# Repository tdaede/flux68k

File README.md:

flux68k
=======

The flux68k is an adapter board that allows usage of Gotek floppy drive emulators running [FlashFloppy](https://github.com/keirf/flashfloppy) firmware with the Sharp X68000 line of computers.

Requirements
------------

1. Two Gotek floppy emulators based on the AT32F435 with SFRKC30.AT4.35 PCB revision (sold as FlashFloppy+ compatible).

2. Two USB flash drives.

3. flux68k PCB.

4. DC +5V power supply with a 6x2.1mm center positive barrel jack (unless using auto switch board)

5. Male to male DB37 cable.

Installation
------------

1. Set the jumpers on each of the Gotek emulators to S0 and MOR.

2. Install the emulators into the flux68k PCB, being careful to line up the power connectors.

3. Plug in the +5V power supply and ensure that both emulators power on.

4. Build the following branch of FlashFloppy, and flash it to to the Gotek. https://github.com/keirf/flashfloppy/pull/781

5. Copy the [example FF.CFG](https://github.com/keirf/flashfloppy/blob/a0a06fc15bd6ab05d6b62a67390bd5e57fd1853e/examples/FF.CFG) to each of the USB sticks and change the pin02 line to:
``` ini
pin02 = in
```

6. Set the switch on the back of the flux68k to drives 2-3.

7. Plug in the DB37 cable between the X68000 and the flux68k.

Usage
-----

Copy floppy images to the USB flash drives and access or boot from them from the X68000. More detailed information on using FlashFloppy can be found at (FlashFloppy's documentation)[https://github.com/keirf/flashfloppy/wiki].

Notes
-----

* XDF images must be renamed to have the .img extension.

* Many applications do not boot correctly from drives 2-3. For these, the rear switch must be set to drives 0-1, and the X68000's internal drives disconnected (unless the auto switch board is used, see below). On compact models, there is a switch on the back of the X68000 to switch the internal drive assigments to 2-3.

* The flux68k must be powered when attached to the X68000 or floppies may not read correctly.

* FlashFloppy currently ignores the motorized eject signal, so the floppy must be manually ejected (by pushing the rotary knob) if an application tries to automatically eject a floppy.

Auto switch board
=================

Optionally, a mod can be installed on non-compact models to automatically switch the internal floppy drive assignments. In addition, this board will also supply power to the external floppy emulators, so that an external power supply is not needed.

Requirements
------------

1. Auto switcher board

2. 34 pin IDC cable, at least 20cm Long

3. +5V internal power cable, either a [Molex to berg connector cable](https://www.crystalfontz.com/product/wrpwry12-four-pin-power-splitter-cable) or a custom made cable that attaches to one of the 3 pin berg connections for the floppy drives or HDD.

Installation
------------

1. Remove the left panel of the X68000.

2. Disconnect the SCSI cable from the external SCSI connector PCB, if present.

3. Disconnect the floppy cable from the external floppy connector PCB.

4. Unscrew and remove the SCSI/floppy connector module via the two plastic tapping screws holding it in place.

5. Remove the SCSI connector PCB from the module by removing the two machine screws holding it in place.

6. Remove the floppy connector PCB from the mdoule by removing the two machine screws holding it in place. Note the relative positions of the bracket and EMI shielding.

7. Attach the new 34 pin IDC cable to the "MB" connector on the auto switcher PCB.

8. Attach the +5V power cable to the swapper PCB.

9. Install the auto switcher PCB on the original metal bracket / EMI shield using the two machine screws.

10. Install the SCSI connector board (if present) on top of the swapper PCB with two machine screws.

11. Install the external connector module back into the X68000 using the two plastic tapping screws.

12. Attach the +5V cable to the appropriate location (the molex connector if using a molex to berg cable).

13. Connect the existing 34 pin floppy IDC cable coming off of the floppy drives to the "FD" connector on the swapper PCB.

14. Disconnect the other end of the existing 34 pin floppy IDC cable from the motherboard connector at the base of the X68000. Leave this disconnected inside the machine.

15. Connect the other end of the new 34 pin IDC cable (connected to the "MB" connector on the switcher PCB) to the motherboard connector at the base of the X68000.

16. Reinstall the left panel of the X68000.

Notes
-----

* The auto switcher PCB uses the previously unused pin 3 of the 37-pin connector as the switch signal. When left floating or high, it switches the internal drives to 0-1. When pulled low, it switches the internal drives to 2-3.

* The auto swticher PCB uses unused pins 18 and 19 of the 37-pin connector to send +5V power to the external floppy emulator. Each pin is protected by a 250mA PTC fuse.

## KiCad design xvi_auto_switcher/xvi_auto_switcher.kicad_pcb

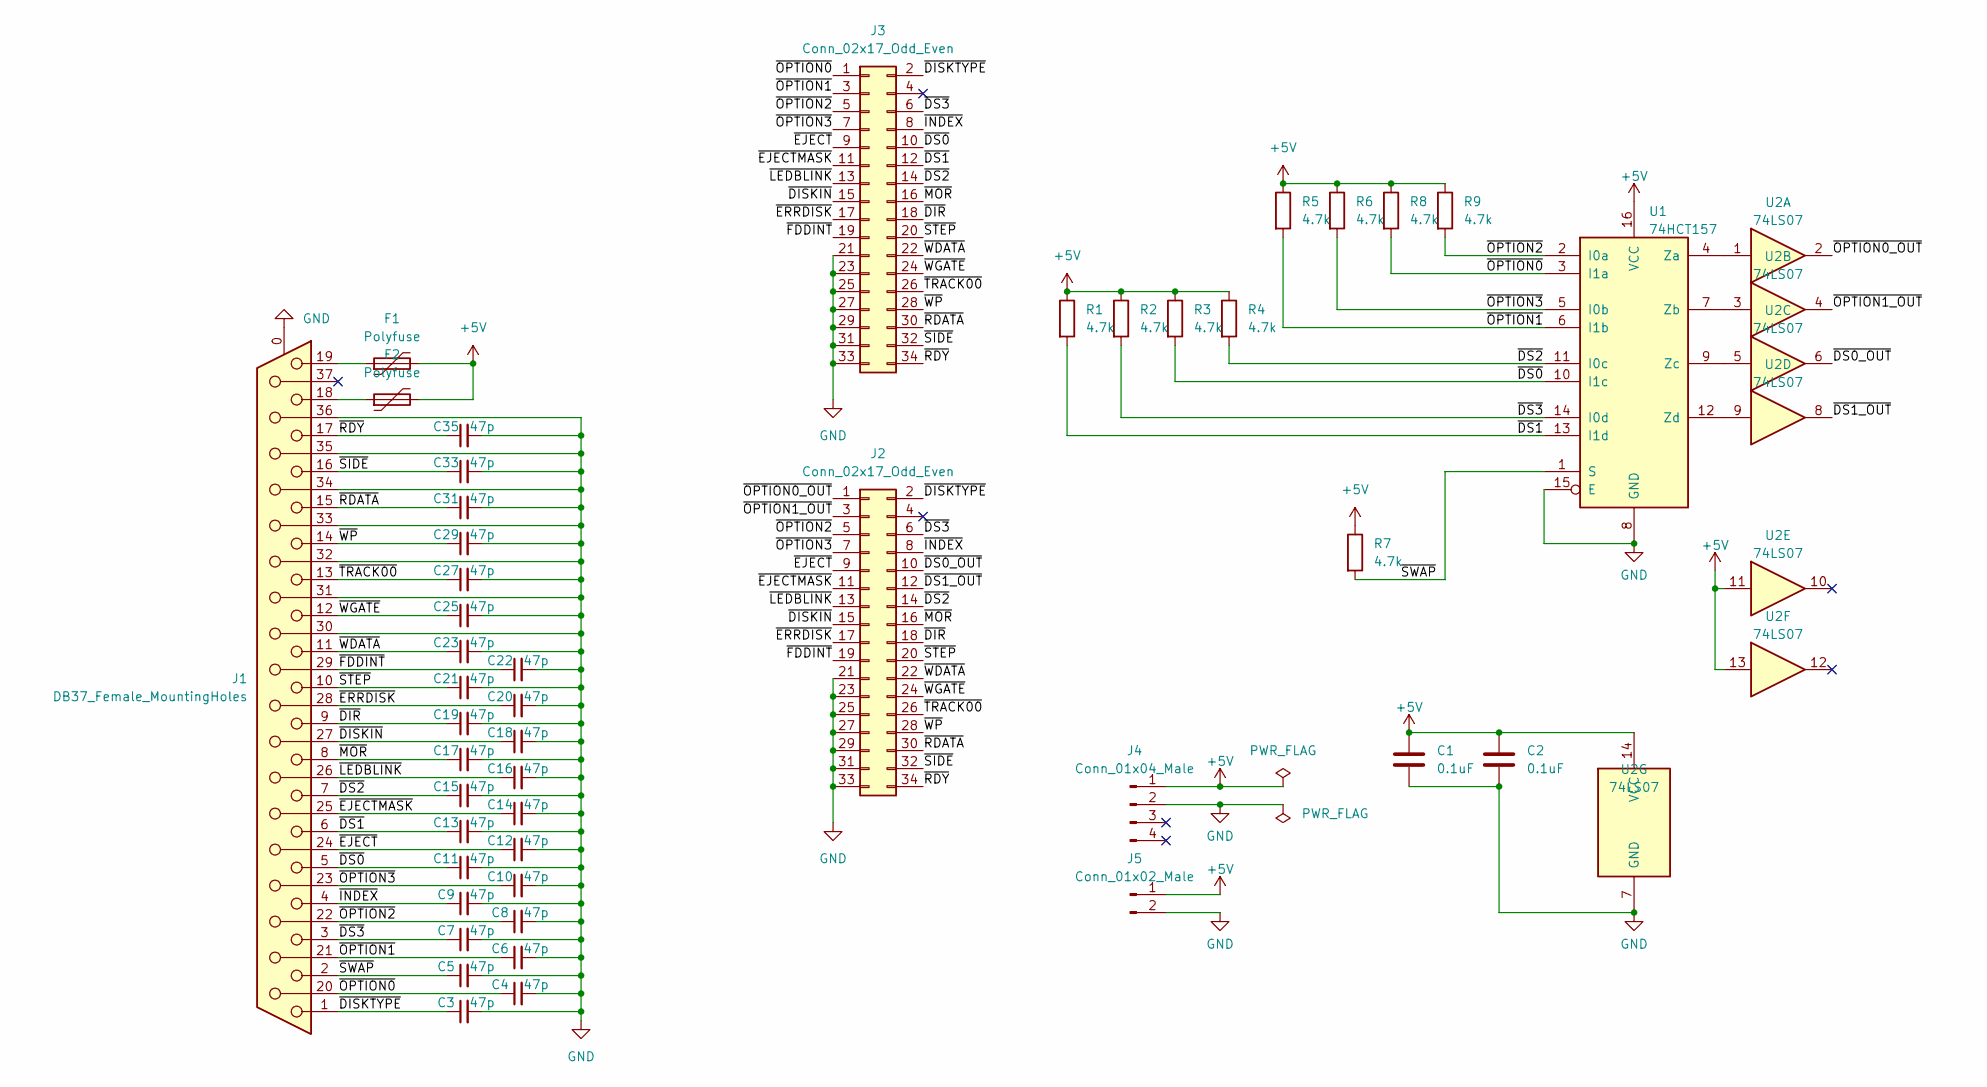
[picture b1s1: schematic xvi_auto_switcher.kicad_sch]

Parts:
C1, C2: 0.1uF; C_0603_1608Metric; Digikey 311-1088-1-ND
C3, C4, C5, C6, C7, C8, C9, C10, C11, C12, C13, C14, C15, C16, C17, C18, C19, C20, C21, C22, C23, C25, C27, C29, C31, C33, C35: 47p; C_0603_1608Metric; Digikey 311-1065-1-ND
F1, F2: Polyfuse; R_1206_3216Metric; Digikey 507-1799-1-ND
J1: DB37_Female_MountingHoles; DSUB-37_Female_Horizontal_P2.77x2.84mm_EdgePinOffset7.70mm_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; Digikey A32114-ND
J2, J3: Conn_02x17_Odd_Even; IDC-Header_2x17_P2.54mm_Vertical; Digikey ED10528-ND
J4: Conn_01x04_Male; PinHeader_1x04_P2.54mm_Horizontal; Digikey A112643-ND
J5: Conn_01x02_Male; PinHeader_1x02_P2.54mm_Vertical; Digikey DNP
R1, R2, R3, R4, R5, R6, R7, R8, R9: 4.7k; R_0603_1608Metric; Digikey 311-4.70KHRCT-ND
U1: 74HCT157; SOIC-16_3.9x9.9mm_P1.27mm; Digikey 296-31835-1-ND
U2: 74LS07; SOIC-14_3.9x8.7mm_P1.27mm; Digikey 296-14877-1-ND

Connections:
+5V: C1.1, C2.1, F1.2, F2.2, J4.1, J5.1, R1.1, R2.1, R3.1, R4.1, R5.1, R6.1, R7.1, R8.1, R9.1, U1.16 (VCC), U2.11, U2.13, U2.14 (VCC)
/~DIR: C19.1, J1.9, J2.18, J3.18
/~DISKIN: C18.1, J1.27, J2.15, J3.15
/~DISKTYPE: C3.1, J1.1, J2.2, J3.2
/~DS0_OUT: J2.10, U2.6
/~DS0: C11.1, J1.5, J3.10, R3.2, U1.10 (I1c)
/~DS1_OUT: J2.12, U2.8
/~DS1: C13.1, J1.6, J3.12, R1.2, U1.13 (I1d)
/~DS2: C15.1, J1.7, J2.14, J3.14, R4.2, U1.11 (I0c)
/~DS3: C7.1, J1.3, J2.6, J3.6, R2.2, U1.14 (I0d)
/~EJECTMASK: C14.1, J1.25, J2.11, J3.11
/~EJECT: C12.1, J1.24, J2.9, J3.9
/~ERRDISK: C20.1, J1.28, J2.17, J3.17
/~FDDINT: C22.1, J1.29, J2.19, J3.19
/~INDEX: C9.1, J1.4, J2.8, J3.8
/~LEDBLINK: C16.1, J1.26, J2.13, J3.13
/~MOR: C17.1, J1.8, J2.16, J3.16
/~OPTION0_OUT: J2.1, U2.2
/~OPTION0: C4.1, J1.20, J3.1, R8.2, U1.3 (I1a)
/~OPTION1_OUT: J2.3, U2.4
/~OPTION1: C6.1, J1.21, J3.3, R5.2, U1.6 (I1b)
/~OPTION2: C8.1, J1.22, J2.5, J3.5, R9.2, U1.2 (I0a)
/~OPTION3: C10.1, J1.23, J2.7, J3.7, R6.2, U1.5 (I0b)
/~RDATA: C31.1, J1.15, J2.30, J3.30
/~RDY: C35.1, J1.17, J2.34, J3.34
/~SIDE: C33.1, J1.16, J2.32, J3.32
/~STEP: C21.1, J1.10, J2.20, J3.20
/~SWAP: C5.1, J1.2, R7.2, U1.1 (S)
/~TRACK00: C27.1, J1.13, J2.26, J3.26
/~WDATA: C23.1, J1.11, J2.22, J3.22
/~WGATE: C25.1, J1.12, J2.24, J3.24
/~WP: C29.1, J1.14, J2.28, J3.28
GND: C1.2, C2.2, C3.2, C4.2, C5.2, C6.2, C7.2, C8.2, C9.2, C10.2, C11.2, C12.2, C13.2, C14.2, C15.2, C16.2, C17.2, C18.2, C19.2, C20.2, C21.2, C22.2, C23.2, C25.2, C27.2, C29.2, C31.2, C33.2, C35.2, J1.0 (PAD), J1.30, J1.31, J1.32, J1.33, J1.34, J1.35, J1.36, J2.21, J2.23, J2.25, J2.27, J2.29, J2.31, J2.33, J3.21, J3.23, J3.25, J3.27, J3.29, J3.31, J3.33, J4.2, J5.2, U1.8 (GND), U1.15 (E), U2.7 (GND)
unnamed: F1.1, J1.19
unnamed: F2.1, J1.18
unnamed: U1.4 (Za), U2.1
unnamed: U1.7 (Zb), U2.3
unnamed: U1.9 (Zc), U2.5
unnamed: U1.12 (Zd), U2.9

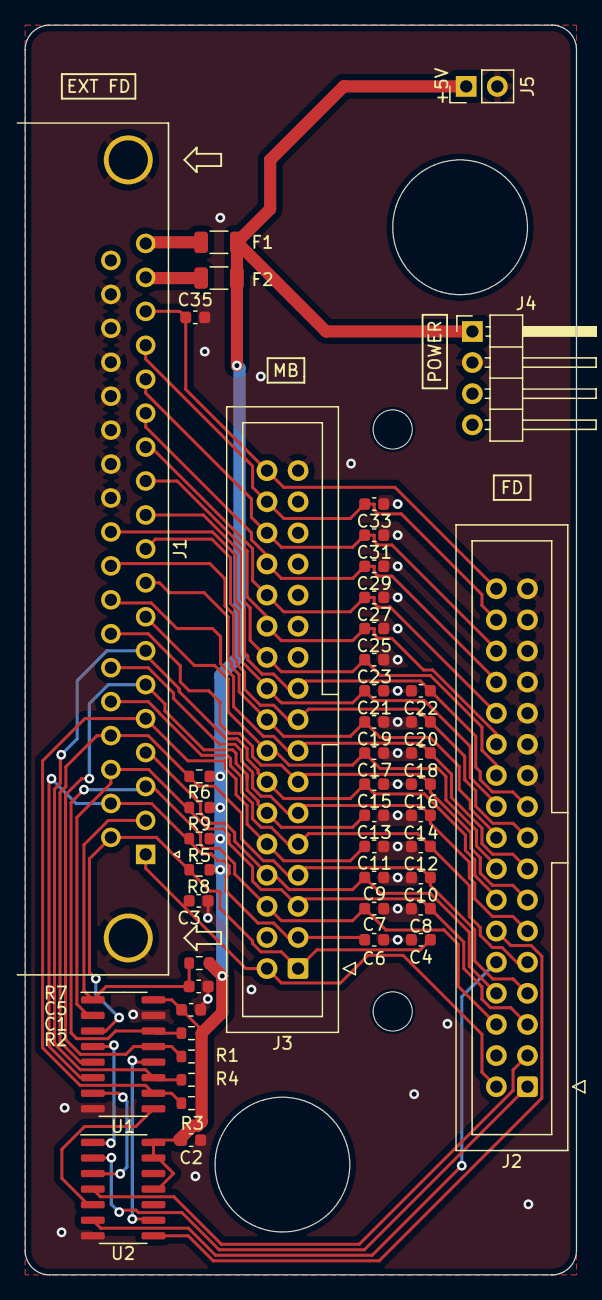
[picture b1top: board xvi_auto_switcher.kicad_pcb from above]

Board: 2 copper layers, 45.0 x 102.0 mm, 47 parts (0 on the bottom side), 39 nets.

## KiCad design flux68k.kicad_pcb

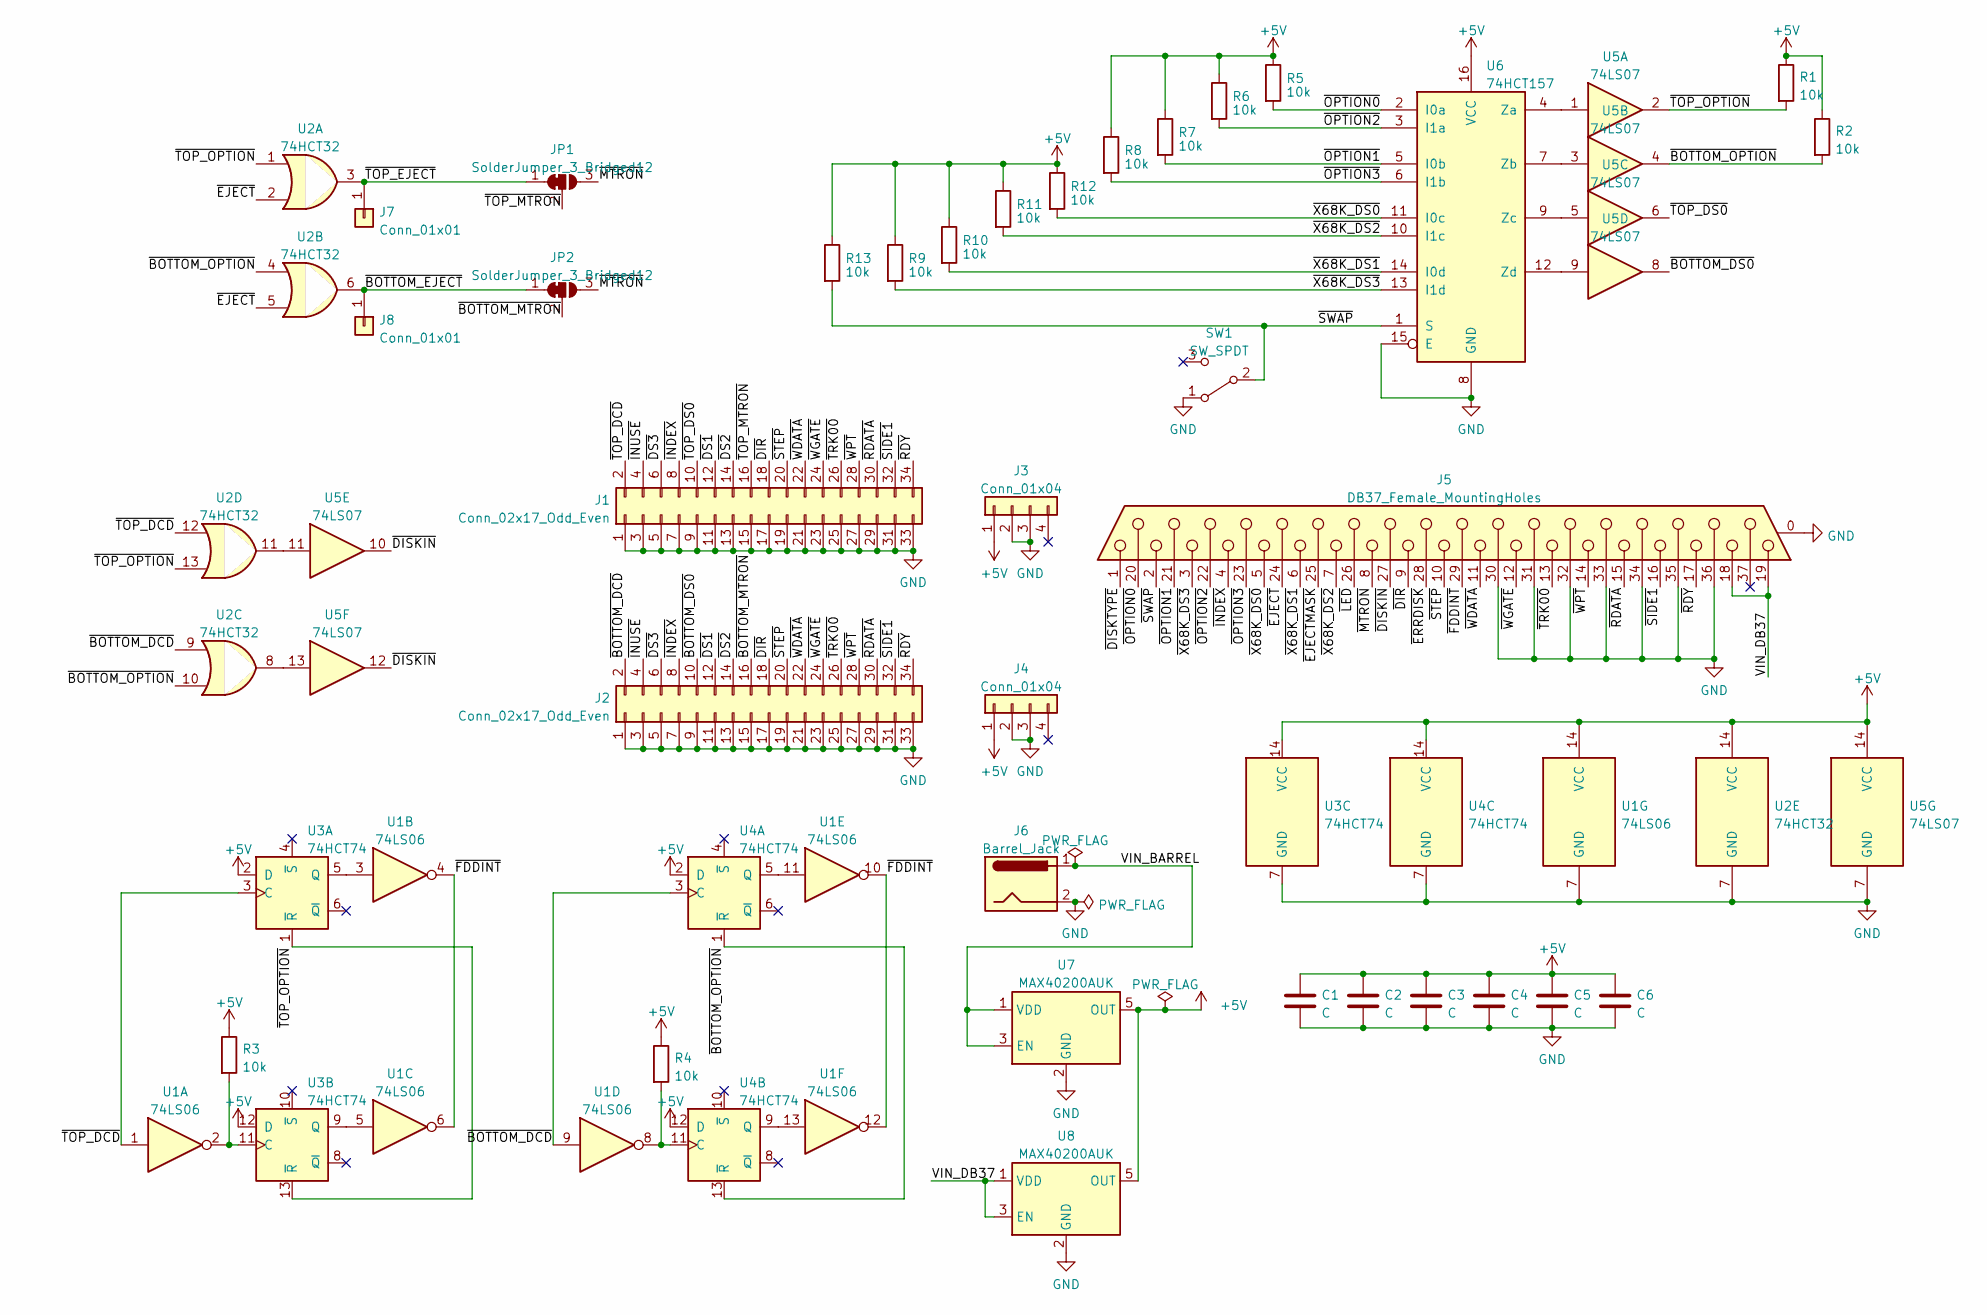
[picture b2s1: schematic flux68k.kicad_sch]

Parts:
C1, C2, C3, C4, C5, C6: C; C_0805_2012Metric_Pad1.18x1.45mm_HandSolder; Digikey 311-1140-1-ND
J1, J2: Conn_02x17_Odd_Even; PinSocket_2x17_P2.54mm_Vertical; Digikey S9199-ND
J3, J4: Conn_01x04; PinSocket_1x04_P2.54mm_Vertical; Digikey S7037-ND
J5: DB37_Female_MountingHoles; DSUB-37_Female_Vertical_P2.77x2.84mm_MountingHoles; Digikey L77SDCH37SOL2-ND
J6: Barrel_Jack; PJ-044AH; Digikey CP-044AH-ND
J7, J8: Conn_01x01; PinSocket_1x01_P2.54mm_Vertical; Digikey DNP
JP1, JP2: SolderJumper_3_Bridged12; SolderJumper-3_P1.3mm_Bridged2Bar12_Pad1.0x1.5mm; Digikey DNP
R1, R2, R3, R4, R5, R6, R7, R8, R9, R10, R11, R12, R13: 10k; R_0805_2012Metric_Pad1.20x1.40mm_HandSolder; Digikey 311-10.0KCRCT-ND
SW1: SW_SPDT; SW_Slide_1P2T_CK_OS102011MS2Q; Digikey CKN12284-ND
U1: 74LS06; SOIC-14_3.9x8.7mm_P1.27mm; Digikey 296-14876-1-ND
U2: 74HCT32; SOIC-14_3.9x8.7mm_P1.27mm; Digikey 296-14868-1-ND
U3, U4: 74HCT74; SOIC-14_3.9x8.7mm_P1.27mm; Digikey 296-1211-1-ND
U5: 74LS07; SOIC-14_3.9x8.7mm_P1.27mm; Digikey 296-14877-1-ND
U6: 74HCT157; SOIC-16_3.9x9.9mm_P1.27mm; Digikey 296-31835-1-ND
U7, U8: MAX40200AUK; SOT-23-5; Digikey MAX40200AUK+TCT-ND

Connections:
+5V: C1.1, C2.1, C3.1, C4.1, C5.1, C6.1, J3.1, J4.1, R1.1, R2.1, R3.1, R4.1, R5.1, R6.1, R7.1, R8.1, R9.1, R10.1, R11.1, R12.1, R13.1, U1.14 (VCC), U2.14 (VCC), U3.2 (D), U3.12 (D), U3.14 (VCC), U4.2 (D), U4.12 (D), U4.14 (VCC), U5.14 (VCC), U6.16 (VCC), U7.5 (OUT), U8.5 (OUT)
/VIN_BARREL: J6.1, U7.1 (VDD), U7.3 (EN)
/VIN_DB37: J5.18, J5.19, U8.1 (VDD), U8.3 (EN)
/~BOTTOM_DCD: J2.2, U1.9, U2.9, U4.3 (C)
/~BOTTOM_DS0: J2.10, U5.8
/~BOTTOM_EJECT: J8.1, JP2.1 (A), U2.6
/~BOTTOM_MTRON: J2.16, JP2.2 (C)
/~BOTTOM_OPTION: R2.2, U2.4, U2.10, U4.1 (~R), U4.13 (~R), U5.4
/~DIR: J1.18, J2.18, J5.9
/~DISKIN: J5.27, U5.10, U5.12
/~DISKTYPE: J5.1
/~DS1: J1.12, J2.12
/~DS2: J1.14, J2.14
/~DS3: J1.6, J2.6
/~EJECTMASK: J5.25
/~EJECT: J5.24, U2.2, U2.5
/~ERRDISK: J5.28
/~FDDINT: J5.29, U1.4, U1.6, U1.10, U1.12
/~INDEX: J1.8, J2.8, J5.4
/~INUSE: J1.4, J2.4
/~LED: J5.26
/~MTRON: J5.8, JP1.3 (B), JP2.3 (B)
/~OPTION0: J5.20, R5.2, U6.2 (I0a)
/~OPTION1: J5.21, R7.2, U6.5 (I0b)
/~OPTION2: J5.22, R6.2, U6.3 (I1a)
/~OPTION3: J5.23, R8.2, U6.6 (I1b)
/~RDATA: J1.30, J2.30, J5.15
/~RDY: J1.34, J2.34, J5.17
/~SIDE1: J1.32, J2.32, J5.16
/~STEP: J1.20, J2.20, J5.10
/~SWAP: J5.2, R13.2, SW1.2 (B), U6.1 (S)
/~TOP_DCD: J1.2, U1.1, U2.12, U3.3 (C)
/~TOP_DS0: J1.10, U5.6
/~TOP_EJECT: J7.1, JP1.1 (A), U2.3
/~TOP_MTRON: J1.16, JP1.2 (C)
/~TOP_OPTION: R1.2, U2.1, U2.13, U3.1 (~R), U3.13 (~R), U5.2
/~TRK00: J1.26, J2.26, J5.13
/~WDATA: J1.22, J2.22, J5.11
/~WGATE: J1.24, J2.24, J5.12
/~WPT: J1.28, J2.28, J5.14
/~X68K_DS0: J5.5, R12.2, U6.11 (I0c)
/~X68K_DS1: J5.6, R10.2, U6.14 (I0d)
/~X68K_DS2: J5.7, R11.2, U6.10 (I1c)
/~X68K_DS3: J5.3, R9.2, U6.13 (I1d)
GND: C1.2, C2.2, C3.2, C4.2, C5.2, C6.2, J1.1, J1.3, J1.5, J1.7, J1.9, J1.11, J1.13, J1.15, J1.17, J1.19, J1.21, J1.23, J1.25, J1.27, J1.29, J1.31, J1.33, J2.1, J2.3, J2.5, J2.7, J2.9, J2.11, J2.13, J2.15, J2.17, J2.19, J2.21, J2.23, J2.25, J2.27, J2.29, J2.31, J2.33, J3.2, J3.3, J4.2, J4.3, J5.0 (PAD), J5.30, J5.31, J5.32, J5.33, J5.34, J5.35, J5.36, J6.2, SW1.1 (A), U1.7 (GND), U2.7 (GND), U3.7 (GND), U4.7 (GND), U5.7 (GND), U6.8 (GND), U6.15 (E), U7.2 (GND), U8.2 (GND)
unnamed: U2.8, U5.13
unnamed: U2.11, U5.11
unnamed: U1.3, U3.5 (Q)
unnamed: R3.2, U1.2, U3.11 (C)
unnamed: U1.5, U3.9 (Q)
unnamed: U1.11, U4.5 (Q)
unnamed: R4.2, U1.8, U4.11 (C)
unnamed: U1.13, U4.9 (Q)
unnamed: U5.1, U6.4 (Za)
unnamed: U5.3, U6.7 (Zb)
unnamed: U5.5, U6.9 (Zc)
unnamed: U5.9, U6.12 (Zd)

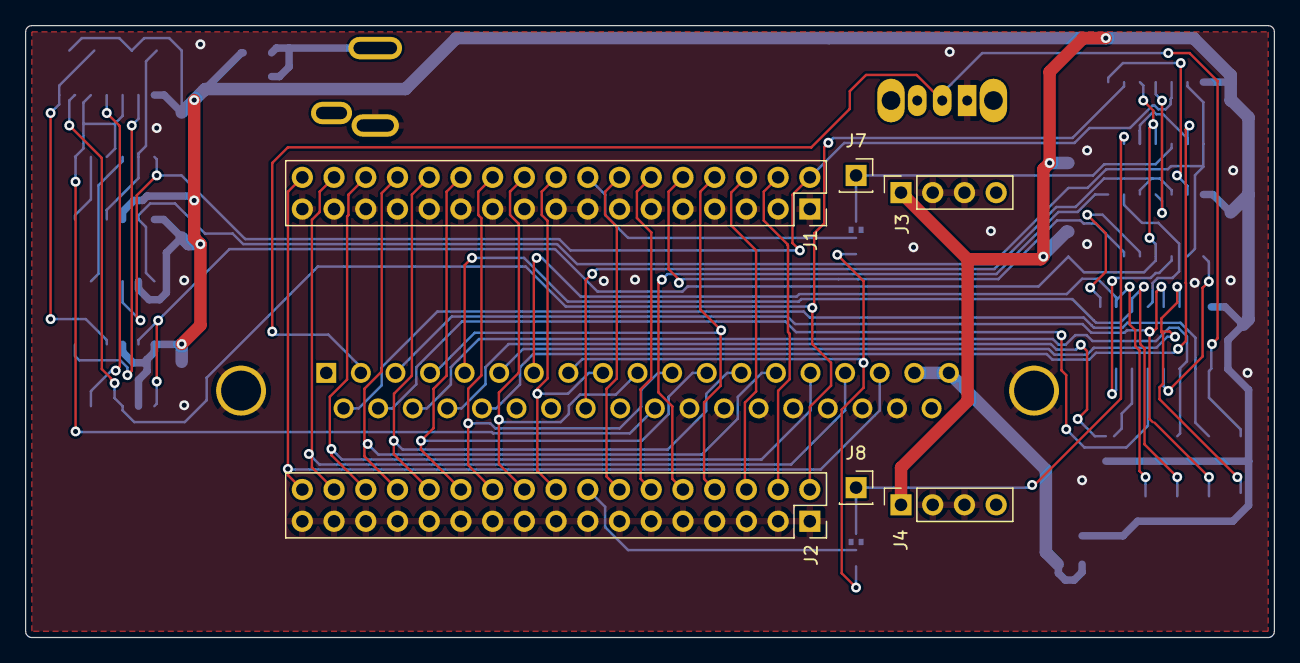
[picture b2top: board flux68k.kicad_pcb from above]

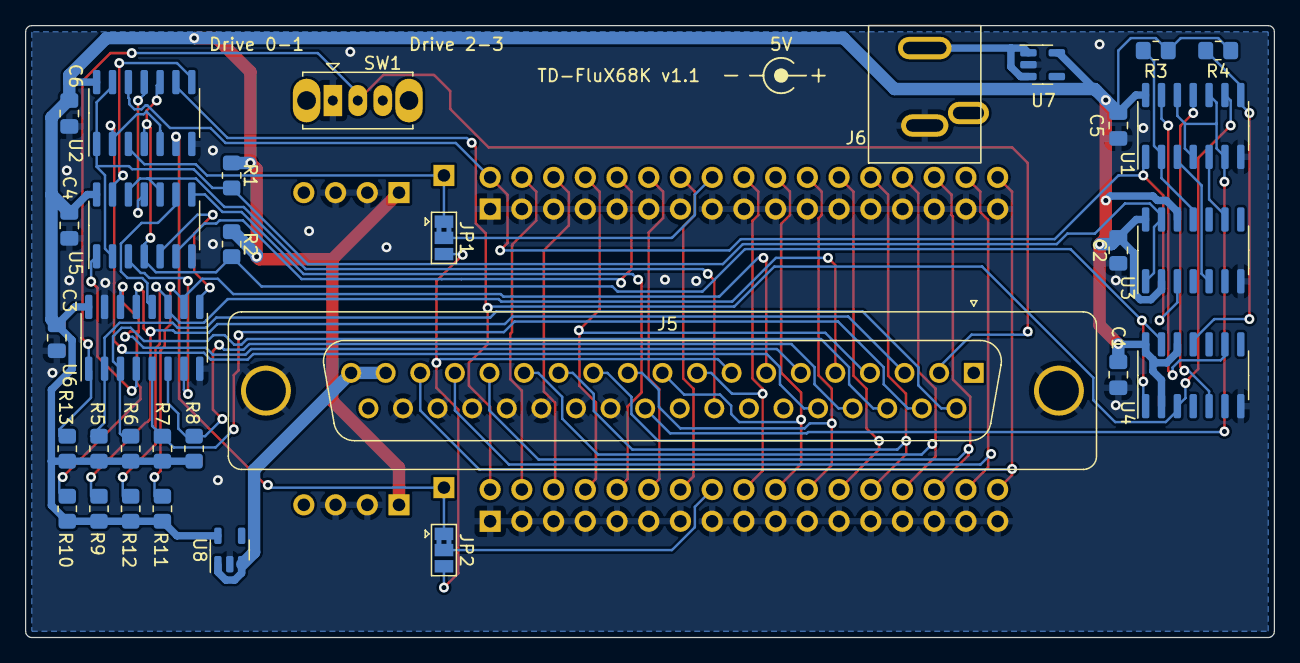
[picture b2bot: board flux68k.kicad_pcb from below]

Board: 2 copper layers, 100.0 x 49.0 mm, 38 parts (32 on the bottom side), 53 nets.

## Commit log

2023-04-22 Add xvi auto switcher board.
2023-04-22 add missing flux68k pullups
2023-04-24 Add README
2023-05-05 add docs for auto switcher pcb
2023-07-30 update auto switcher pcb connector positions and add caps
2023-07-30 add pullups and ideal diodes to flux68k
2023-08-20 shrink board by 1mm
2023-08-20 generate flux68k 1.1
2023-12-27 v1.1

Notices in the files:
xvi_auto_switcher/xvi_auto_switcher.kicad_pcb:
CERN-OHL-S 2023
